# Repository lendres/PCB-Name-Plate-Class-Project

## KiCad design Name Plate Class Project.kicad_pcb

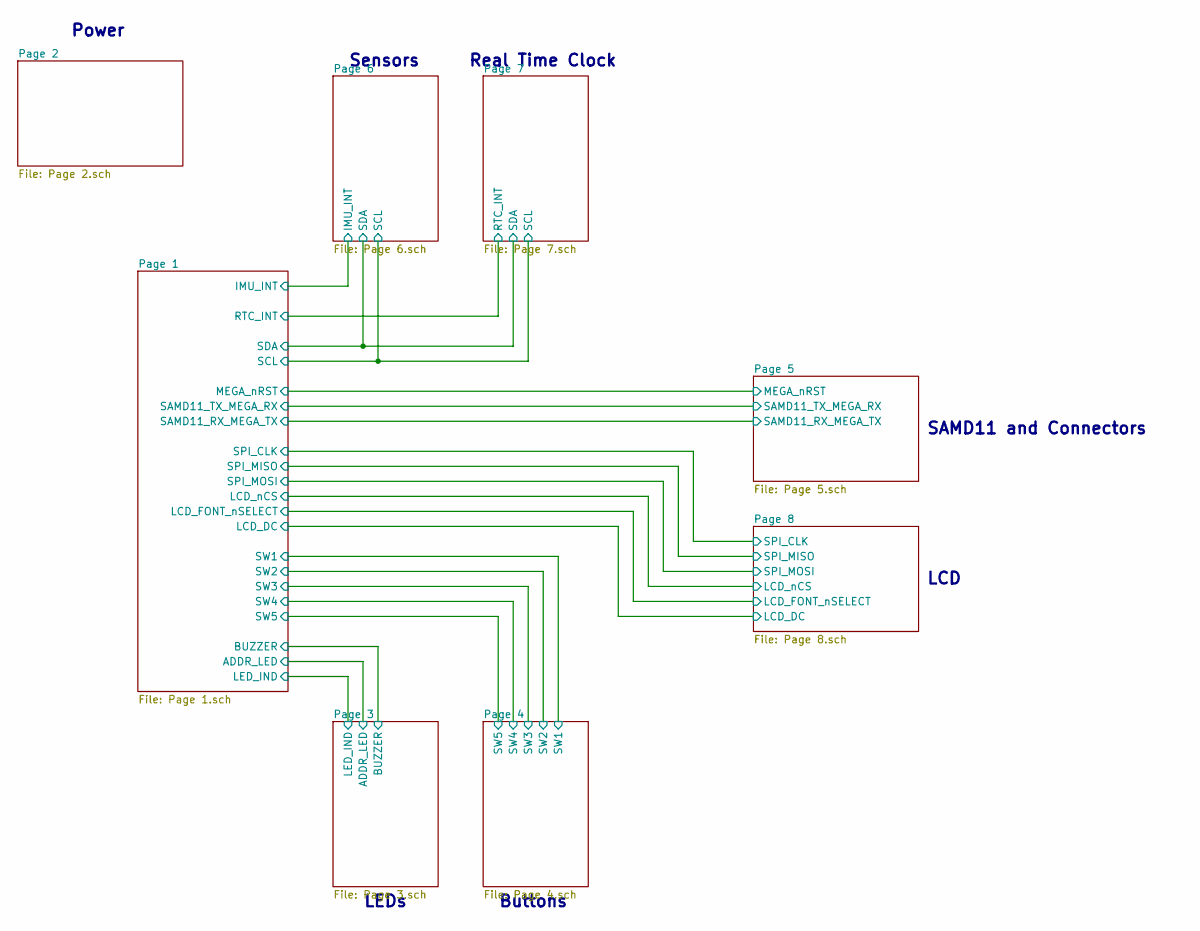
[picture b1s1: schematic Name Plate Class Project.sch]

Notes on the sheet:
LCD
SAMD11 and Connectors
Real Time Clock
Sensors
Power
LEDs
Buttons

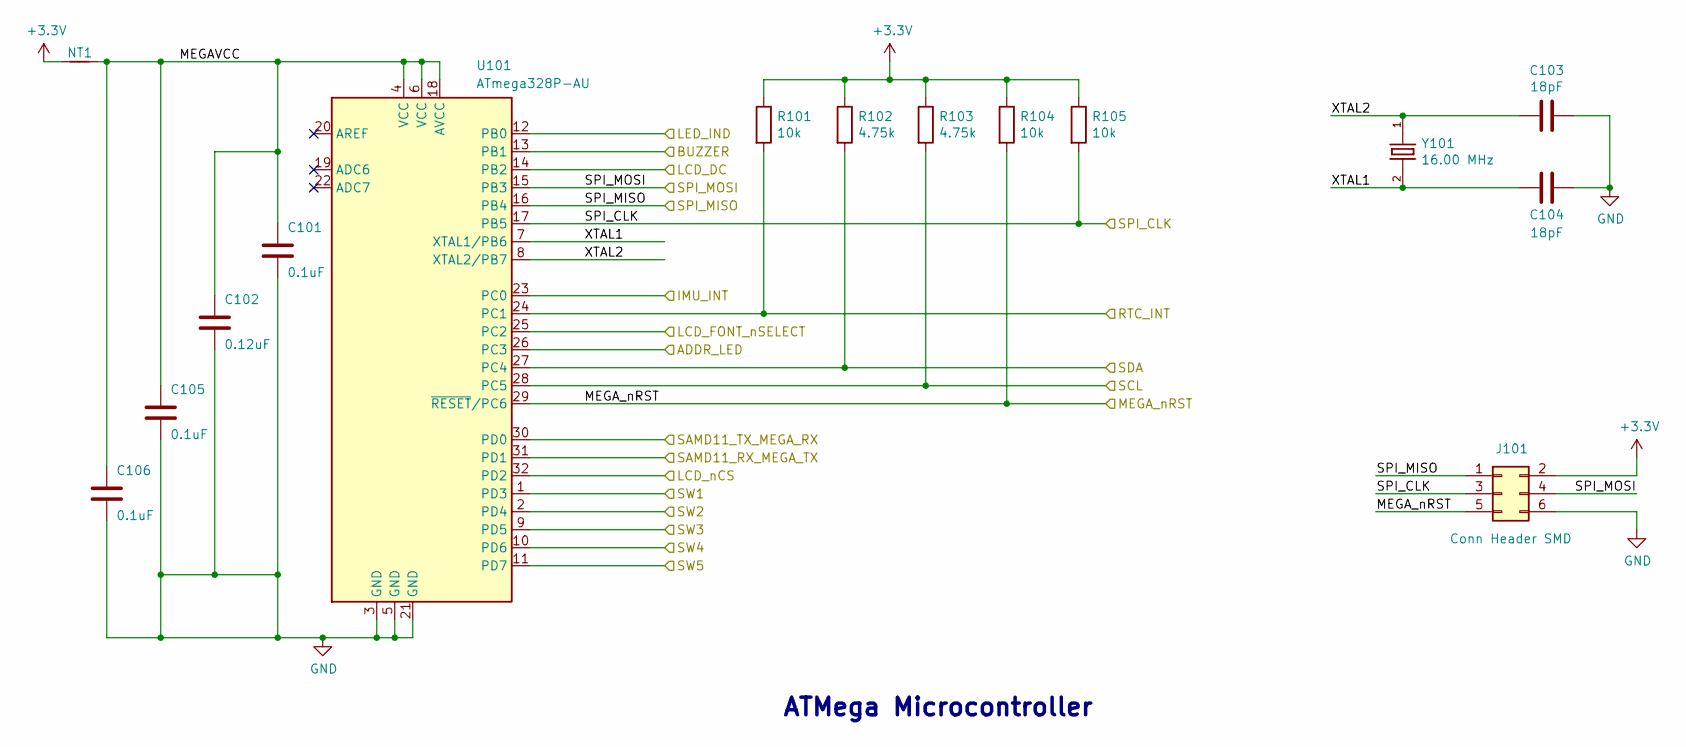
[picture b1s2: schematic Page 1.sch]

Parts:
C101, C105, C106: 0.1uF; C_0603_1608Metric_Pad1.05x0.95mm_HandSolder; Mftr Part No. CC0603KPX7R7BB104; DigiKey Part No. 311-1335-1-ND
C102: 0.12uF; C_0805_2012Metric_Pad1.15x1.40mm_HandSolder; Mftr Part No. 08053C124KAT2A; DigiKey Part No. 478-5161-1-ND
C103, C104: 18pF; C_0603_1608Metric_Pad1.05x0.95mm_HandSolder; Mftr Part No. C0603C180J5GACTU; DigiKey Part No. 399-1052-1-ND
J101: Conn Header SMD; Molex_PinHeader_2x03; Mftr Part No. 713085406; DigiKey Part No. 0713085406-ND
NT1: Net-Tie_2; NetTie-2_SMD_Pad0.5mm; Mftr Part No. None; DigiKey Part No. None
R101, R104, R105: 10k; R_0603_1608Metric_Pad1.05x0.95mm_HandSolder; Mftr Part No. RC0603JR-0710KL; DigiKey Part No. 311-10KGRCT-ND
R102, R103: 4.75k; R_0603_1608Metric_Pad1.05x0.95mm_HandSolder; Mftr Part No. RC0603JR-074K7L; DigiKey Part No. 311-10KGRCT-ND
U101: ATmega328P-AU; TQFP-32_7x7mm_P0.8mm; Mftr Part No. ATMega328P-AU; DigiKey Part No. ATMEGA328P-AURCT-ND
Y101: 16.00 MHz; Oscillator_ABM3-16.000MHZ-B2-T; Mftr Part No. ABM3-16.000MHZ-B2-T; DigiKey Part No. 535-9103-1-ND

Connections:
+3V3: J101.2, NT1.1, R101.1, R102.1, R103.1, R104.1, R105.1; also elsewhere on the board
/Page 1/ADDR_LED: U101.26 (PC3); also elsewhere on the board
/Page 1/BUZZER: U101.13 (PB1); also elsewhere on the board
/Page 1/IMU_INT: U101.23 (PC0); also elsewhere on the board
/Page 1/LCD_DC: U101.14 (PB2); also elsewhere on the board
/Page 1/LCD_FONT_nSELECT: U101.25 (PC2); also elsewhere on the board
/Page 1/LCD_nCS: U101.32 (PD2); also elsewhere on the board
/Page 1/LED_IND: U101.12 (PB0); also elsewhere on the board
/Page 1/MEGAVCC: C101.1, C102.1, C105.1, C106.1, NT1.2, U101.4 (VCC), U101.6 (VCC), U101.18 (AVCC)
/Page 1/MEGA_nRST: J101.5, R104.2, U101.29 (~RESET~/PC6); also elsewhere on the board
/Page 1/RTC_INT: R101.2, U101.24 (PC1); also elsewhere on the board
/Page 1/SAMD11_RX_MEGA_TX: U101.31 (PD1); also elsewhere on the board
/Page 1/SAMD11_TX_MEGA_RX: U101.30 (PD0); also elsewhere on the board
/Page 1/SCL: R103.2, U101.28 (PC5); also elsewhere on the board
/Page 1/SDA: R102.2, U101.27 (PC4); also elsewhere on the board
/Page 1/SPI_CLK: J101.3, R105.2, U101.17 (PB5); also elsewhere on the board
/Page 1/SPI_MISO: J101.1, U101.16 (PB4); also elsewhere on the board
/Page 1/SPI_MOSI: J101.4, U101.15 (PB3); also elsewhere on the board
/Page 1/SW1: U101.1 (PD3); also elsewhere on the board
/Page 1/SW2: U101.2 (PD4); also elsewhere on the board
/Page 1/SW3: U101.9 (PD5); also elsewhere on the board
/Page 1/SW4: U101.10 (PD6); also elsewhere on the board
/Page 1/SW5: U101.11 (PD7); also elsewhere on the board
/Page 1/XTAL1: C104.2, U101.7 (XTAL1/PB6), Y101.2
/Page 1/XTAL2: C103.2, U101.8 (XTAL2/PB7), Y101.1
GND: C101.2, C102.2, C103.1, C104.1, C105.2, C106.2, J101.6, U101.3 (GND), U101.5 (GND), U101.21 (GND); also elsewhere on the board

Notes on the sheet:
ATMega Microcontroller

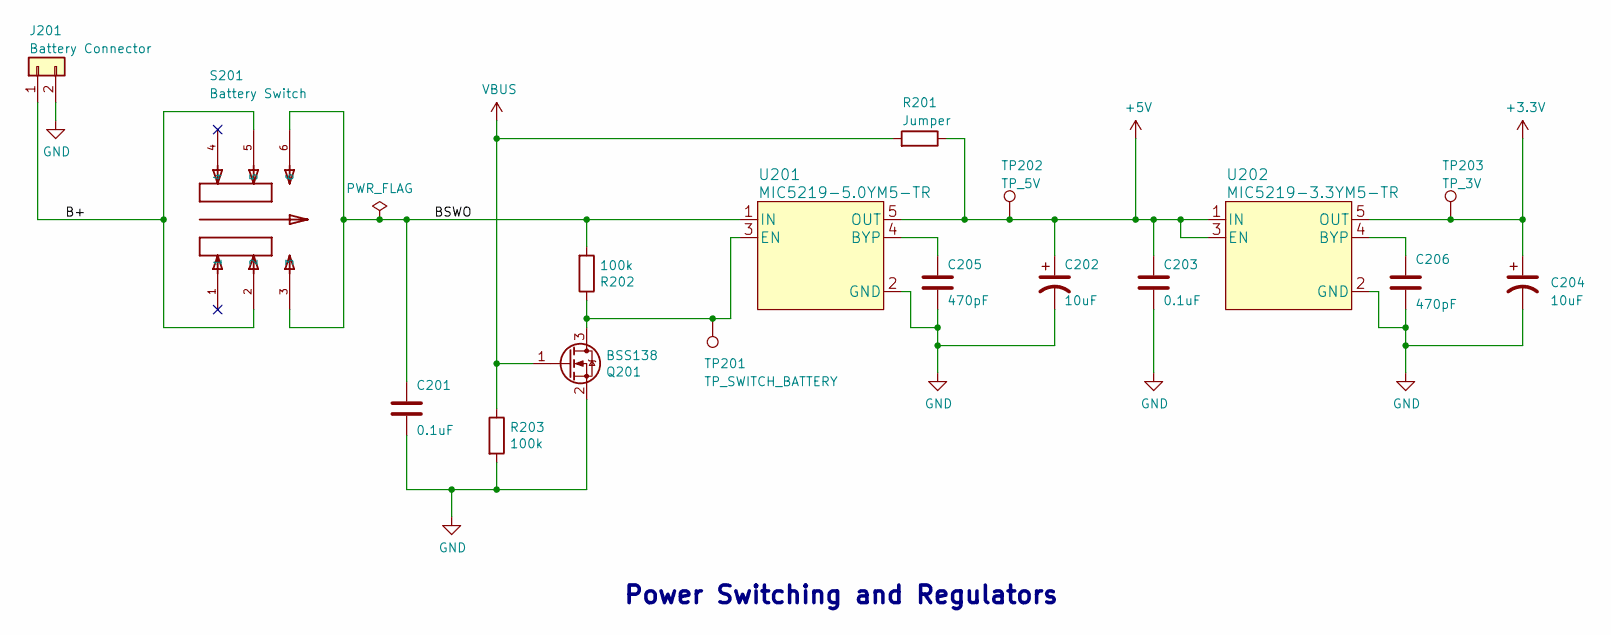
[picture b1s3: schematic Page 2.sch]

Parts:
C201, C203: 0.1uF; C_0603_1608Metric_Pad1.05x0.95mm_HandSolder; Mftr Part No. CC0603KPX7R7BB104; DigiKey Part No. 311-1335-1-ND
C202, C204: 10uF; T491A106K010AT; Mftr Part No. T491A106K010AT; DigiKey Part No. 399-3684-1-ND
C205, C206: 470pF; C_0603_1608Metric_Pad1.05x0.95mm_HandSolder; Mftr Part No. CC0603MRX7R9BB471; DigiKey Part No. 311-3377-1-ND
J201: Battery Connector; JST_PH_w_SolderPoints; Mftr Part No. S2B-PH-SM4-TB(LF)(SN); DigiKey Part No. 455-1749-1-ND
Q201: BSS138; SOT-23; Mftr Part No. BSS138; DigiKey Part No. BSS138CT-ND
R201: Jumper; R_0603_1608Metric_Pad1.05x0.95mm_HandSolder; Mftr Part No. 311-10KGRCT-ND; DigiKey Part No. RC0603JR-070RL
R202, R203: 100k; R_0603_1608Metric_Pad1.05x0.95mm_HandSolder; Mftr Part No. RC0603JR-07100KL; DigiKey Part No. 311-100KGRCT-ND
S201: Battery Switch; Switch_JS202011SCQN; Mftr Part No. JS202011SCQN; DigiKey Part No. 401-2002-1-ND
TP201, TP202, TP203: Test Point; Pad_2.5-2.5; Mftr Part No. None; DigiKey Part No. None
U201: MIC5219-5.0YM5-TR; SOT-23-5_HandSoldering; Mftr Part No. MIC5219-5.0YM5-TR; DigiKey Part No. 576-2770-6-ND
U202: MIC5219-3.3YM5-TR; SOT-23-5_HandSoldering; Mftr Part No. MIC5219-3.3YM5-TR; DigiKey Part No. 576-1281-6-ND

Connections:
+3V3: C204.1 (+), TP203.1, U202.5 (OUT); also elsewhere on the board
+5V: C202.1 (+), C203.1, R201.1, TP202.1, U201.5 (OUT), U202.1 (IN), U202.3 (EN); also elsewhere on the board
/Page 2/B+: J201.1, S201.2, S201.5
/Page 2/BSWO: C201.1, R202.2, S201.3, S201.6, U201.1 (IN)
GND: C201.2, C202.2 (-), C203.2, C204.2 (-), C205.2, C206.2, J201.2, Q201.2 (S), R203.2, U201.2 (GND), U202.2 (GND); also elsewhere on the board
unnamed: C205.1, U201.4 (BYP)
unnamed: C206.1, U202.4 (BYP)
unnamed: Q201.3 (D), R202.1, TP201.1, U201.3 (EN)
VBUS: Q201.1 (G), R201.2, R203.1; also elsewhere on the board

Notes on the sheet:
Power Switching and Regulators

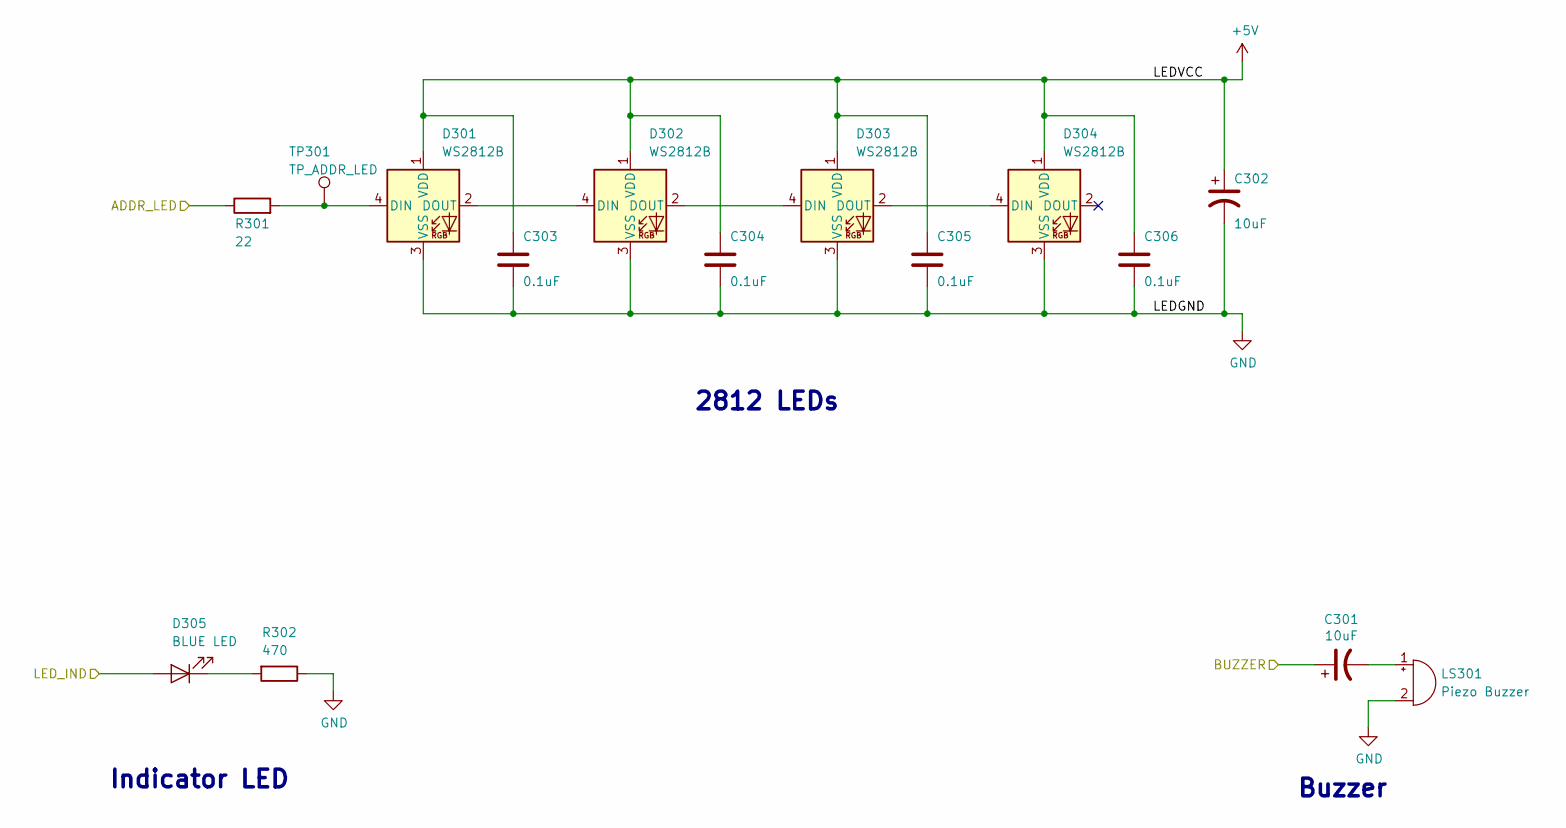
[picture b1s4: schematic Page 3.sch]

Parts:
C301, C302: 10uF; T491A106K010AT; Mftr Part No. T491A106K010AT; DigiKey Part No. 399-3684-1-ND
C303, C304, C305, C306: 0.1uF; C_0603_1608Metric_Pad1.05x0.95mm_HandSolder; Mftr Part No. CC0603KPX7R7BB104; DigiKey Part No. 311-1335-1-ND
D301, D302, D303, D304: WS2812B; LED_WS2812B_PLCC4_5.0x5.0mm_P3.2mm; Mftr Part No. 3094; DigiKey Part No. 1528-2388-ND
D305: BLUE LED; LED_G-GX; Mftr Part No. LB Q39G-L2OO-35-1; DigiKey Part No. 475-2816-1-ND
LS301: Piezo Buzzer; Buzzer_TDK_PS1240P02BT_D12.2mm_H6.5mm; Mftr Part No. AB1541B-LW100-R; DigiKey Part No. 668-1448-ND
R301: 22; R_0603_1608Metric_Pad1.05x0.95mm_HandSolder; Mftr Part No. CRGCQ0603J22R; DigiKey Part No. A130081CT-ND
R302: 470; R_0603_1608Metric_Pad1.05x0.95mm_HandSolder; Mftr Part No. CRGCQ0603J470R; DigiKey Part No. A130089CT-ND
TP301: Test Point; Pad_2.5-2.5; Mftr Part No. None; DigiKey Part No. None

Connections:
+5V: C302.1 (+), C303.1, C304.1, C305.1, C306.1, D301.1 (VDD), D302.1 (VDD), D303.1 (VDD), D304.1 (VDD); also elsewhere on the board
/Page 1/ADDR_LED: R301.1; also elsewhere on the board
/Page 1/BUZZER: C301.1 (+); also elsewhere on the board
/Page 1/LED_IND: D305.2 (A); also elsewhere on the board
GND: C302.2 (-), C303.2, C304.2, C305.2, C306.2, D301.3 (VSS), D302.3 (VSS), D303.3 (VSS), D304.3 (VSS), LS301.2 (+), R302.1; also elsewhere on the board
unnamed: C301.2 (-), LS301.1 (-)
unnamed: D301.2 (DOUT), D302.4 (DIN)
unnamed: D301.4 (DIN), R301.2, TP301.1
unnamed: D302.2 (DOUT), D303.4 (DIN)
unnamed: D303.2 (DOUT), D304.4 (DIN)
unnamed: D305.1 (K), R302.2

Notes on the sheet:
2812 LEDs
Indicator LED
Buzzer

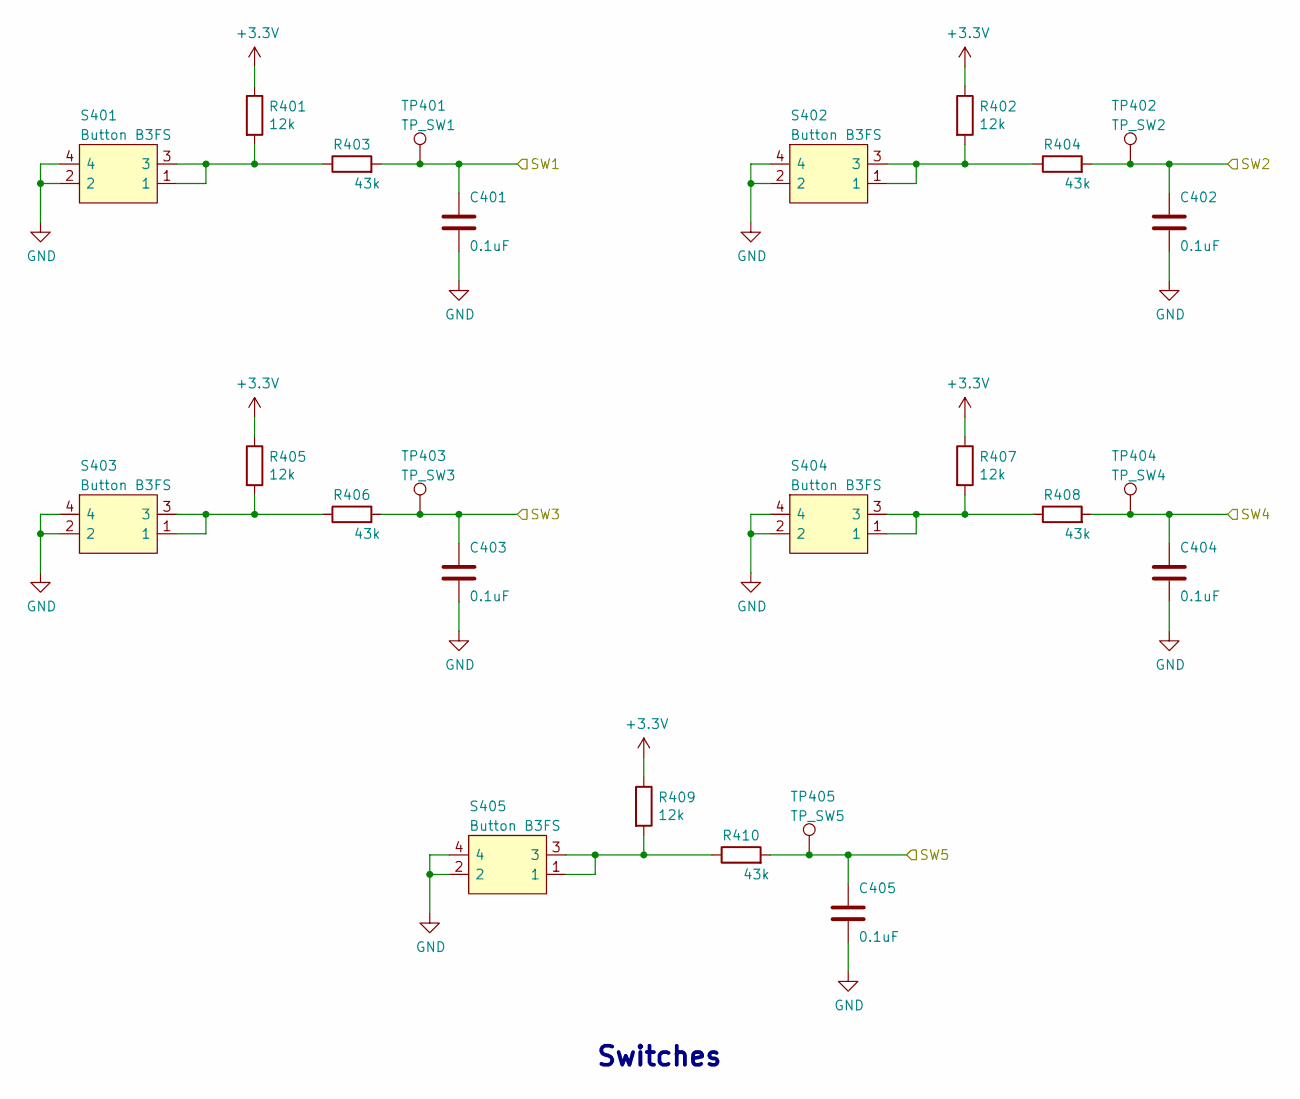
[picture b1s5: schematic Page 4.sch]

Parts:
C401, C402, C403, C404, C405: 0.1uF; C_0603_1608Metric_Pad1.05x0.95mm_HandSolder; Mftr Part No. CC0603KPX7R7BB104; DigiKey Part No. 311-1335-1-ND
R401, R402, R405, R407, R409: 12k; R_0603_1608Metric_Pad1.05x0.95mm_HandSolder; Mftr Part No. RC0603JR-0712KL; DigiKey Part No. 311-12KGRCT-ND
R403, R404, R406, R408, R410: 43k; R_0603_1608Metric_Pad1.05x0.95mm_HandSolder; Mftr Part No. RC0603JR-0743KL; DigiKey Part No. 311-43KGRCT-ND
S401, S402, S403, S404, S405: Button B3FS; Button_B3FS-1000P; Mftr Part No. B3FS-1000P; DigiKey Part No. SW423DKR-ND
TP401, TP402, TP403, TP404, TP405: Test Point; Pad_2.5-2.5; Mftr Part No. None; DigiKey Part No. None

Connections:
+3V3: R401.1, R402.1, R405.1, R407.1, R409.1; also elsewhere on the board
/Page 1/SW1: C401.1, R403.2, TP401.1; also elsewhere on the board
/Page 1/SW2: C402.1, R404.2, TP402.1; also elsewhere on the board
/Page 1/SW3: C403.1, R406.2, TP403.1; also elsewhere on the board
/Page 1/SW4: C404.1, R408.2, TP404.1; also elsewhere on the board
/Page 1/SW5: C405.1, R410.2, TP405.1; also elsewhere on the board
GND: C401.2, C402.2, C403.2, C404.2, C405.2, S401.2, S401.4, S402.2, S402.4, S403.2, S403.4, S404.2, S404.4, S405.2, S405.4; also elsewhere on the board
unnamed: R401.2, R403.1, S401.1, S401.3
unnamed: R402.2, R404.1, S402.1, S402.3
unnamed: R405.2, R406.1, S403.1, S403.3
unnamed: R407.2, R408.1, S404.1, S404.3
unnamed: R409.2, R410.1, S405.1, S405.3

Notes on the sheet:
Switches

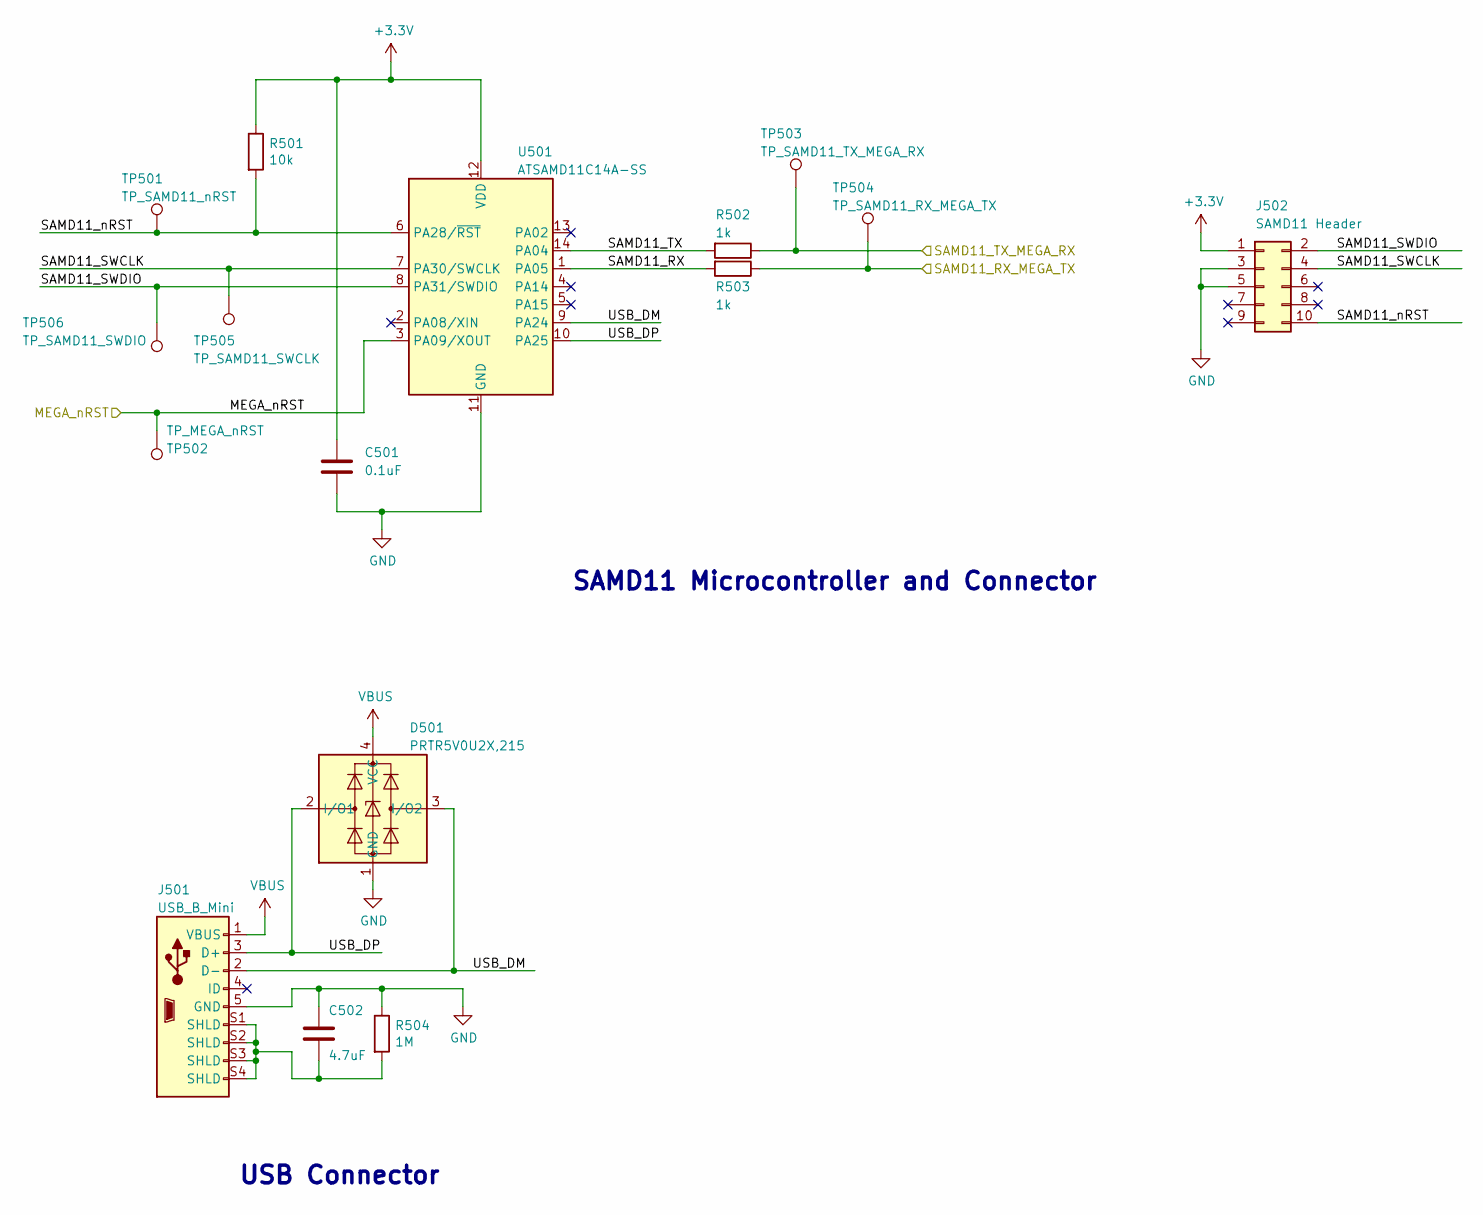
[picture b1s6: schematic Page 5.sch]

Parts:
C501: 0.1uF; C_0603_1608Metric_Pad1.05x0.95mm_HandSolder; Mftr Part No. CC0603KPX7R7BB104; DigiKey Part No. 311-1335-1-ND
C502: 4.7uF; C_0603_1608Metric_Pad1.05x0.95mm_HandSolder; Mftr Part No. C0805C472KDRACTU; DigiKey Part No. 399-6738-1-ND
D501: PRTR5V0U2X,215; SOT-143-4; Mftr Part No. PRTR5V0U2X,215; DigiKey Part No. 1727-3884-6-ND
J501: USB_B_Mini; Molex_USB_Mini_B_548190572; Mftr Part No. 548190572; DigiKey Part No. WM17116DKR-ND
J502: SAMD11 Header; SAMTEC-FTS-105-01-X-DV; Mftr Part No. FTS-105-01-L-DV; DigiKey Part No. SAM1157-05-ND
R501: 10k; R_0603_1608Metric_Pad1.05x0.95mm_HandSolder; Mftr Part No. RC0603JR-0710KL; DigiKey Part No. 311-10KGRCT-ND
R502, R503: 1k; R_0603_1608Metric_Pad1.05x0.95mm_HandSolder; Mftr Part No. RC0603JR-071KL; DigiKey Part No. 311-1.0KGRCT-ND
R504: 1M; R_0603_1608Metric_Pad1.05x0.95mm_HandSolder; Mftr Part No. RC0603FR-071ML; DigiKey Part No. 311-1.00MHRCT-ND
TP501, TP502, TP503, TP504, TP505, TP506: Test Point; Pad_2.5-2.5; Mftr Part No. None; DigiKey Part No. None
U501: ATSAMD11C14A-SS; SOIC-14_3.9x8.7mm_P1.27mm; Mftr Part No. ATSAMD11C14A-SSNT; DigiKey Part No. ATSAMD11C14A-SSNTDKR-ND

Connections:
+3V3: C501.1, J502.1, R501.1, U501.12 (VDD); also elsewhere on the board
/Page 1/MEGA_nRST: TP502.1, U501.3 (PA09/XOUT); also elsewhere on the board
/Page 1/SAMD11_RX_MEGA_TX: R503.1, TP504.1; also elsewhere on the board
/Page 1/SAMD11_TX_MEGA_RX: R502.1, TP503.1; also elsewhere on the board
/Page 5/SAMD11_RX: R503.2, U501.1 (PA05)
/Page 5/SAMD11_SWCLK: J502.4, TP505.1, U501.7 (PA30/SWCLK)
/Page 5/SAMD11_SWDIO: J502.2, TP506.1, U501.8 (PA31/SWDIO)
/Page 5/SAMD11_TX: R502.2, U501.14 (PA04)
/Page 5/SAMD11_nRST: J502.10, R501.2, TP501.1, U501.6 (PA28/~RST)
/Page 5/USB_DM: D501.3 (I/O2), J501.2 (D-), U501.9 (PA24)
/Page 5/USB_DP: D501.2 (I/O1), J501.3 (D+), U501.10 (PA25)
GND: C501.2, C502.1, D501.1 (GND), J501.5 (GND), J502.3, J502.5, R504.1, U501.11 (GND); also elsewhere on the board
unnamed: C502.2, J501.S1 (SHLD), J501.S2 (SHLD), J501.S3 (SHLD), J501.S4 (SHLD), R504.2
VBUS: D501.4 (VCC), J501.1 (VBUS); also elsewhere on the board

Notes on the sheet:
SAMD11 Microcontroller and Connector
USB Connector

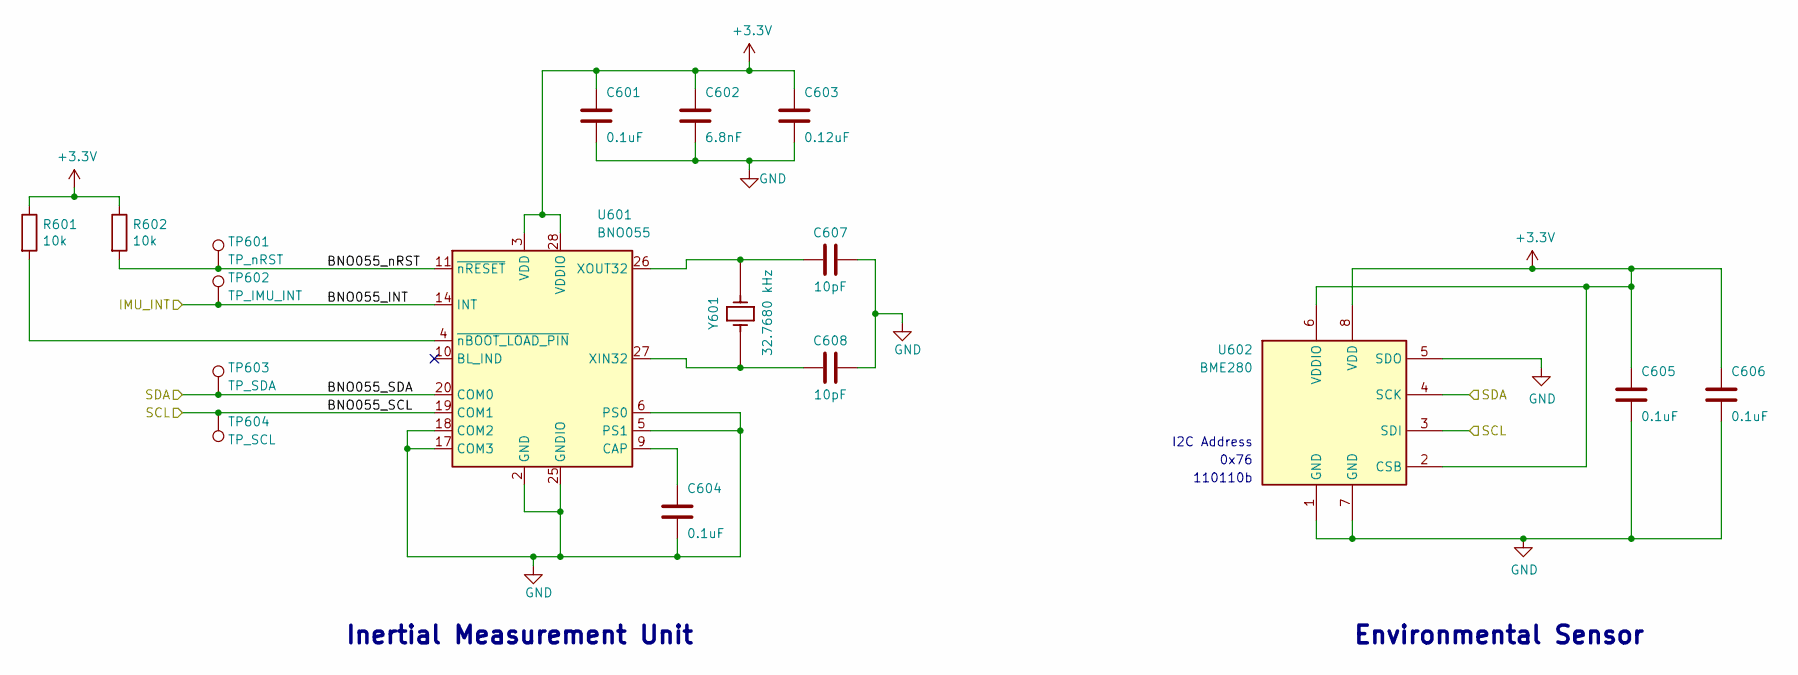
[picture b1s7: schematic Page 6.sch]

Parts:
C601, C604, C605, C606: 0.1uF; C_0603_1608Metric_Pad1.05x0.95mm_HandSolder; Mftr Part No. CC0603KPX7R7BB104; DigiKey Part No. 311-1335-1-ND
C602: 6.8nF; C_0603_1608Metric_Pad1.05x0.95mm_HandSolder; Mftr Part No. CAPC160X80X92L35; DigiKey Part No. 732-7932-1-ND
C603: 0.12uF; C_0805_2012Metric_HandSolder; Mftr Part No. 08053C124KAT2A; DigiKey Part No. 478-5161-1-ND
C607, C608: 10pF; C_0603_1608Metric_Pad1.05x0.95mm_HandSolder; Mftr Part No. C0603C100J1GACTU; DigiKey Part No. 399-7816-1-ND
R601, R602: 10k; R_0603_1608Metric_Pad1.05x0.95mm_HandSolder; Mftr Part No. RC0603JR-0710KL; DigiKey Part No. 311-10KGRCT-ND
TP601, TP602, TP603, TP604: Test Point; Pad_2.5-2.5; Mftr Part No. None; DigiKey Part No. None
U601: BNO055; LGA-28_5.2x3.8mm_P0.5mm; Mftr Part No. BOSCH_BNO055; DigiKey Part No. 828-1058-1-ND
U602: BME280; Bosch_LGA-8_2.5x2.5mm_P0.65mm_ClockwisePinNumbering; Mftr Part No. BOSCH_BME280; DigiKey Part No. 828-1063-1-ND
Y601: 32.7680 kHz; Oscillator_MC-405_32.7680K-D__ROHS; Mftr Part No. MC-405 32.7680K-E3: ROHS; DigiKey Part No. SER4311TR-ND

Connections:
+3V3: C601.1, C602.1, C603.1, C605.1, C606.1, R601.1, R602.1, U601.3 (VDD), U601.28 (VDDIO), U602.2 (CSB), U602.6 (VDDIO), U602.8 (VDD); also elsewhere on the board
/Page 1/IMU_INT: TP602.1, U601.14 (INT); also elsewhere on the board
/Page 1/SCL: TP604.1, U601.19 (COM1), U602.3 (SDI); also elsewhere on the board
/Page 1/SDA: TP603.1, U601.20 (COM0), U602.4 (SCK); also elsewhere on the board
/Page 6/BNO055_nRST: R602.2, TP601.1, U601.11 (~nRESET)
GND: C601.2, C602.2, C603.2, C604.2, C605.2, C606.2, C607.1, C608.1, U601.2 (GND), U601.5 (PS1), U601.6 (PS0), U601.15 (GNDIO), U601.16 (GNDIO), U601.17 (COM3), U601.18 (COM2), U601.25 (GNDIO), U602.1 (GND), U602.5 (SDO), U602.7 (GND); also elsewhere on the board
unnamed: C604.1, U601.9 (CAP)
unnamed: C607.2, U601.26 (XOUT32), Y601.1
unnamed: C608.2, U601.27 (XIN32), Y601.2
unnamed: R601.2, U601.4 (~nBOOT_LOAD_PIN)

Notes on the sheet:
I2C Address
0x76
110110b
Environmental Sensor
Inertial Measurement Unit

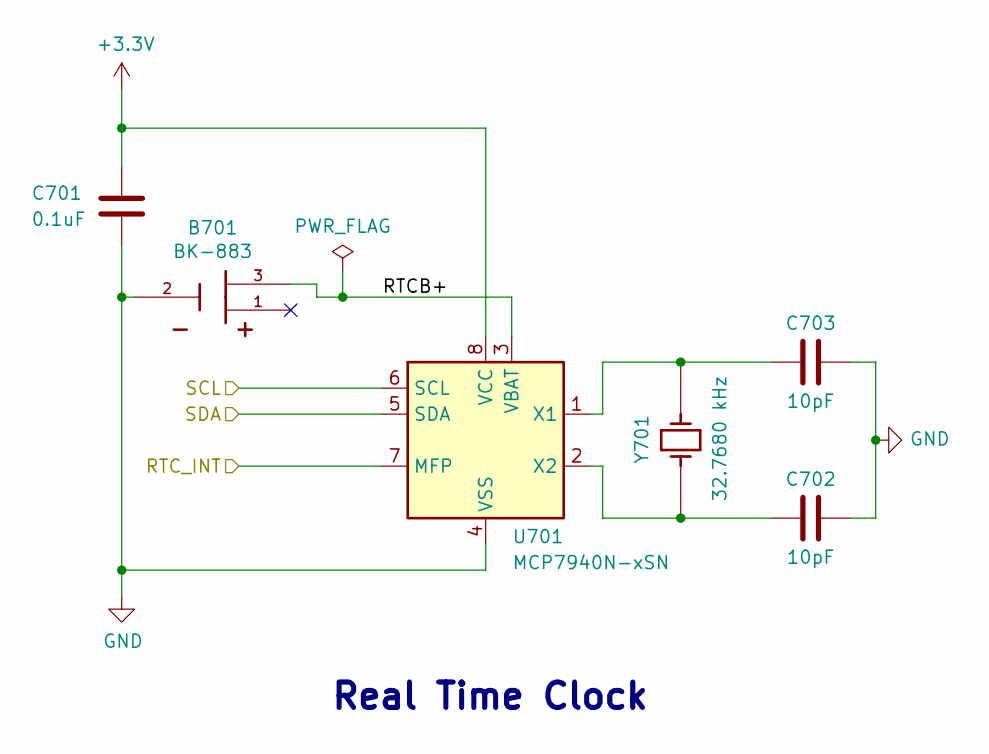
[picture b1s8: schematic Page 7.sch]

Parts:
B701: BK-883; BAT_BK-883; Mftr Part No. BK-883; DigiKey Part No. BK-883-ND
C701: 0.1uF; C_0603_1608Metric_Pad1.05x0.95mm_HandSolder; Mftr Part No. CC0603KPX7R7BB104; DigiKey Part No. 311-1335-1-ND
C702, C703: 10pF; C_0603_1608Metric_Pad1.05x0.95mm_HandSolder; Mftr Part No. C0603C100J1GACTU; DigiKey Part No. 399-7816-1-ND
U701: MCP7940N-xSN; SOIC-8_3.9x4.9mm_P1.27mm; Mftr Part No. MCP79400-I/SN; DigiKey Part No. MCP79400-I/SN-ND
Y701: 32.7680 kHz; Oscillator_MC-405_32.7680K-D__ROHS; Mftr Part No. MC-405 32.7680K-E3: ROHS; DigiKey Part No. SER4311TR-ND

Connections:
+3V3: C701.1, U701.8 (VCC); also elsewhere on the board
/Page 1/RTC_INT: U701.7 (MFP); also elsewhere on the board
/Page 1/SCL: U701.6 (SCL); also elsewhere on the board
/Page 1/SDA: U701.5 (SDA); also elsewhere on the board
/Page 7/RTCB+: B701.3 (VCC), U701.3 (VBAT)
GND: B701.2 (GND), C701.2, C702.1, C703.1, U701.4 (VSS); also elsewhere on the board
unnamed: C702.2, U701.2 (X2), Y701.2
unnamed: C703.2, U701.1 (X1), Y701.1

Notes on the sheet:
Real Time Clock

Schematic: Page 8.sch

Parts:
C801: 0.1uF; C_0603_1608Metric_Pad1.05x0.95mm_HandSolder; Mftr Part No. CC0603KPX7R7BB104; DigiKey Part No. 311-1335-1-ND
J801: DNP; LCD_ER-TFTM024-3_SMD; Mftr Part No. NPTC202KFMS-RC; DigiKey Part No. S5690-ND
R801, R802, R803, R804, R805, R806: 22; R_0603_1608Metric_Pad1.05x0.95mm_HandSolder; Mftr Part No. CRGCQ0603J22R; DigiKey Part No. A130081CT-ND
TP801, TP802, TP803, TP804, TP805, TP806: Test Point; Pad_2.5-2.5; Mftr Part No. None; DigiKey Part No. None

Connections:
+3V3: C801.1, J801.2 (VDD), J801.29 (BL); also elsewhere on the board
/Page 1/LCD_DC: R805.1, TP805.1; also elsewhere on the board
/Page 1/LCD_FONT_nSELECT: R802.1, TP802.1; also elsewhere on the board
/Page 1/LCD_nCS: R806.1, TP806.1; also elsewhere on the board
/Page 1/SPI_CLK: R803.1, TP803.1; also elsewhere on the board
/Page 1/SPI_MISO: R801.1, TP801.1; also elsewhere on the board
/Page 1/SPI_MOSI: R804.1, TP804.1; also elsewhere on the board
/Page 8/LCD_DC_R: J801.25 (LCD_D/C), R805.2
/Page 8/LCD_FONT_nCS: J801.36 (FONT_CS#), R802.2
/Page 8/LCD_SPI_CLK: J801.24 (LCD_CLK), J801.33 (FONT_SCL), R803.2
/Page 8/LCD_SPI_MISO: J801.28 (LCD_SDO), J801.32 (FONT_SDO), R801.2
/Page 8/LCD_SPI_MOSI: J801.27 (LCD_SDI), J801.34 (FONT_SDI), R804.2
/Page 8/LCD_nCS_R: J801.23 (LCD_CS#), R806.2
GND: C801.2, J801.1 (VSS), J801.40 (VSS); also elsewhere on the board

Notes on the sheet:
LCD Screen

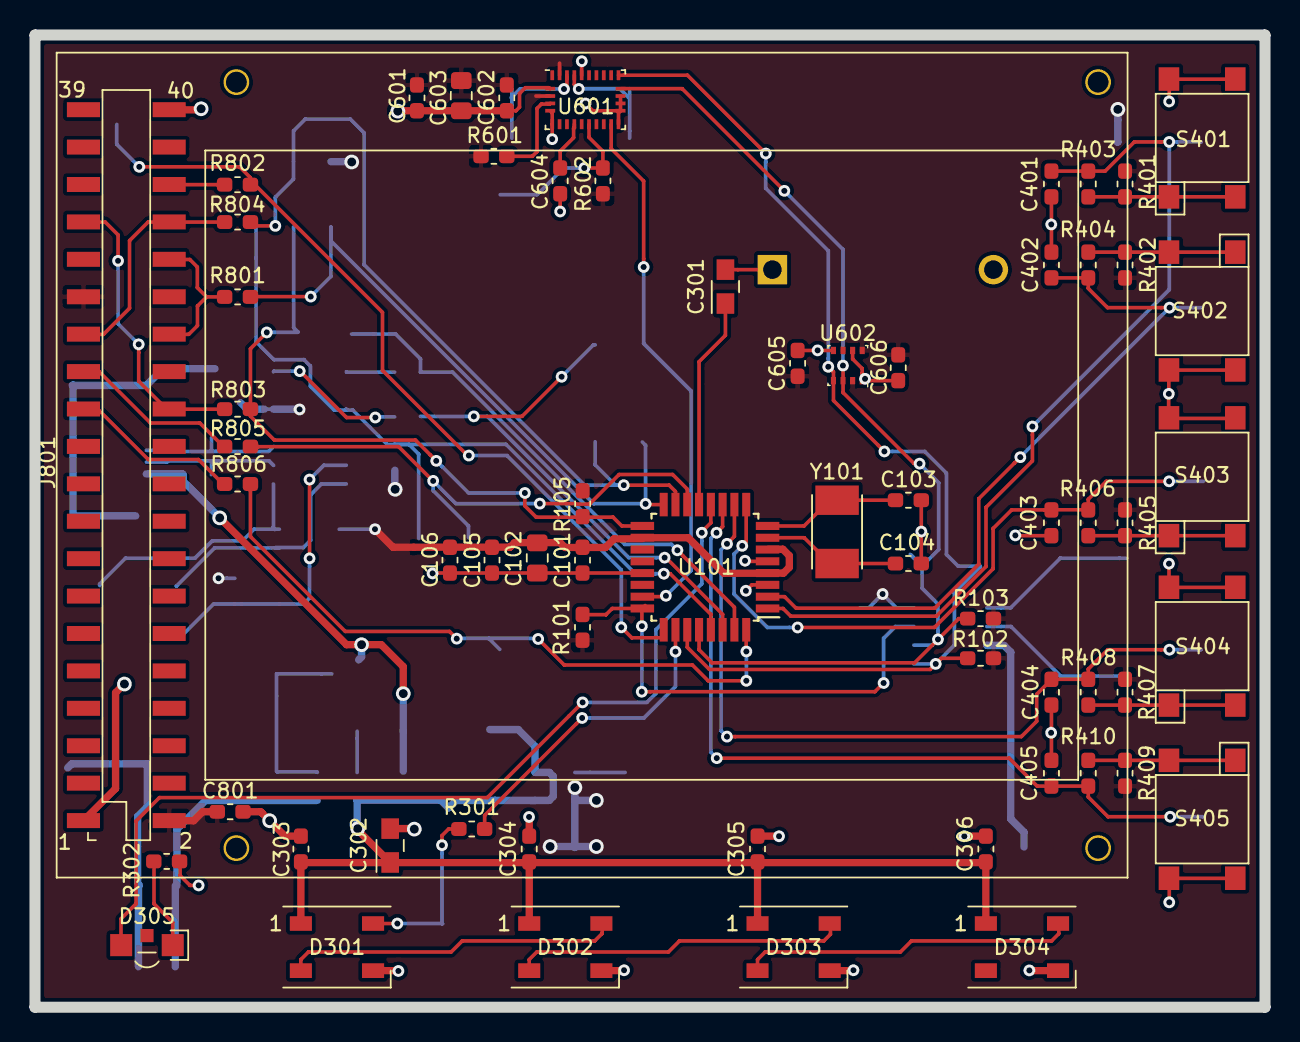
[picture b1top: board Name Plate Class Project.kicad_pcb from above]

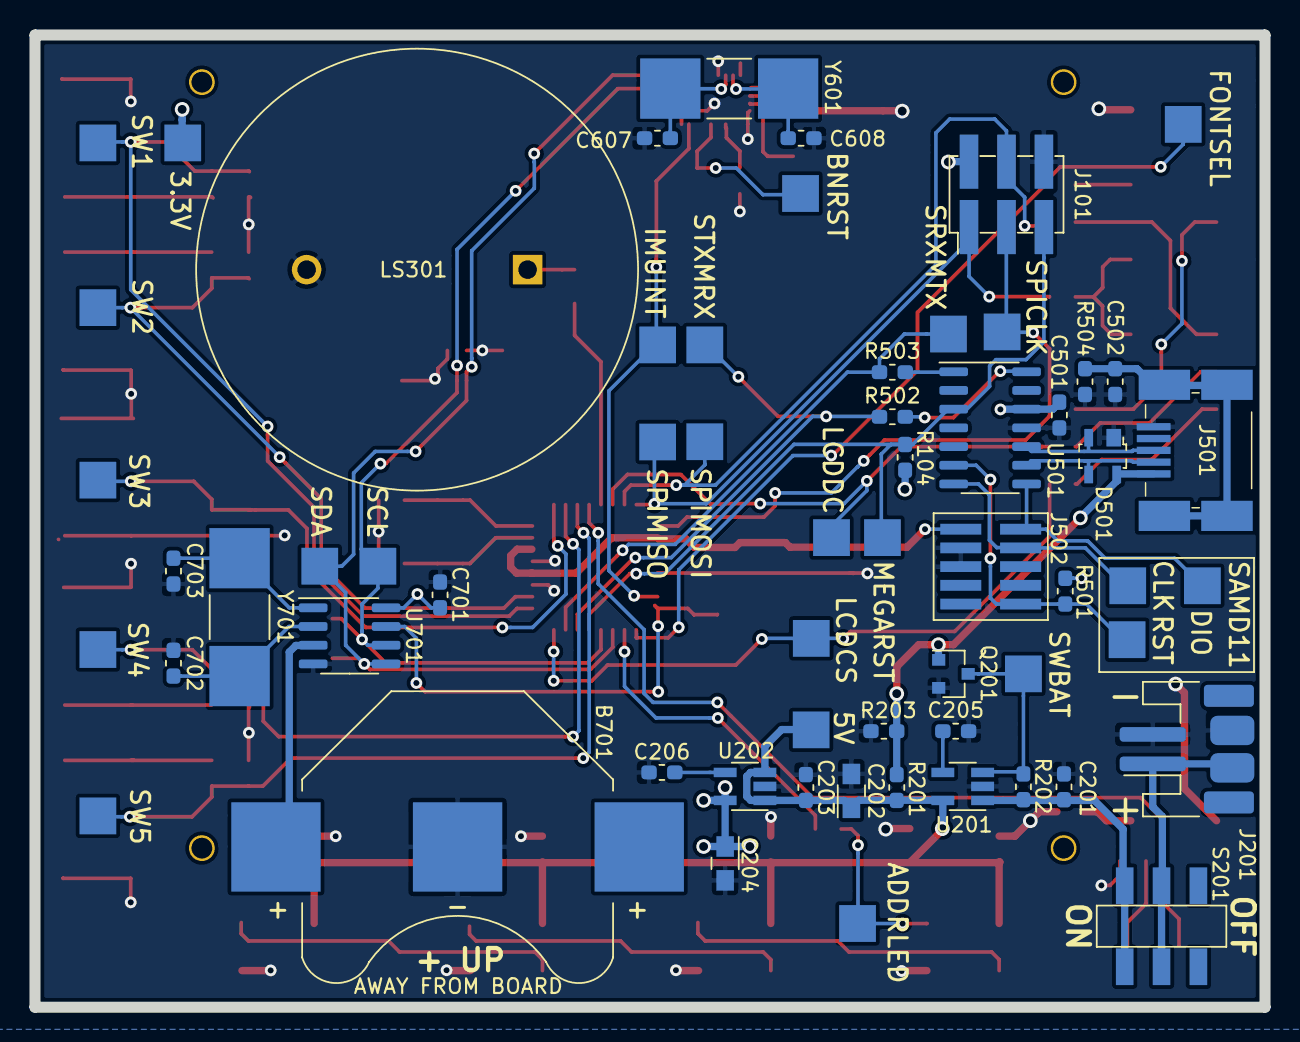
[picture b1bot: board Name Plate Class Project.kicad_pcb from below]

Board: 2 copper layers, 83.5 x 66.0 mm, 125 parts (61 on the bottom side), 66 nets.

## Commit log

2020-05-02 Initial commit of files.
2020-05-16 Switched to Hierarchical
2020-05-17 Updating to Final Revision
2020-05-17 Updating Page Numbering
2020-05-17 Updated Page Numbers
2020-05-19 Updates to schematic
    Switching to ATMega34UF chip.
2020-05-26 As submitted to class
2020-05-30 Library Updates
2020-06-17 PCB Layout
2020-06-17 PCB Update
2020-06-18 PCB Tweaks
2020-06-23 Before removing empty module entries from pcb
2020-07-08 Final Design Files
    Final design files as submitted.
